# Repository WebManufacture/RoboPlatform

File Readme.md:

# RoboPlatform

#### Общее

Универсальная платформа для построения систем цифровой автоматизации и роботизации. Платформа разрабатывается, как самостоятельный проект, развитие идеи Arduino. В качестве основных контроллеров, используемых в платформе, выбрана линейка контроллеров от компании ST Microelectronics (STM8, STM32 ARM).
Основные принципы и идеи платформы:

0. Возможность создания по большей части самовоспроизводимой системы модулей. Имеется ввиду, что на базе существующей системы модулей и инструментов можно создавать как свою копию, так и новые, перспективные.
1. Сделать компоненты настолько дешевыми, чтобы их можно было использовать свободно, как "кирпичики" для построения сложных систем, состоящих из огромного числа отлаженных модулей. Также дешевизна и простота модулей, делает возможным их применение в условиях кризиса или бесконечно-малого финансирования.
2. По контроллеру - в каждый узел! Идея состоит в том, чтобы создать общее программное облако, с помощью которого, можно создавать самоконфигурируемые, самособирающиеся, самотестируемые и другие системы, требующие интерактивности от каждого своего функционального узла от мала до велика. Благо, современная конкуренция на рынке контроллеров дает возможность приобретать 8ми разрядные контроллеры по цене < $0.5, и ARM-контолллеры от 1$.
3. Облегчение и автоматизация труда разработчика. Предполагается применение разработок Web-Manufacture.net (KLAB, HLAB, ILAB и прочих), а также создание современных систем управления, разработки и тестирования для этой платформы. Под "современностью" понимается использования опыта разработки для систем более высокого уровня, применительно, к несколько "поотставшей" области программирования и отладки систем на контроллерах.
4. Использовать коммуникационные протоколы и принципы проекта ILAB
5. "Селективная шина" в качестве основной модели взаимодействия 

#### Текущая стадия и план.

На сегодня разработана и продумана общая концепция проекта. Проект разбит на несколько автономных, но взаимосвязанных подпроектов. Наибольший прогресс в области создания ПО, в частности распределенной клиент-серверной инфраструктуры и пользовательских интерфейсов. 
Реализованы “в железе” основные модули и базовый набор инстументов проекта, как то RoboMotors, RoboMind, RoboPwm, RoboPower, являющиеся концептуальными наследниками своих программных прототипов. 
Некоторые подпроекты уже имеют собственную жизнь, как RoboCNC, RoboPainter и RoboRails, трудящееся в автоматизированых теплицах.
В рамках платформы идет работа по 3м основным направлениям:

1. Инструменты и механическая часть, корпуса модулей, система соединения.
2. Адаптация модулей, для воспроизводства в системе на базе RoboCNC (#МФКС).
3. Доработка ПО, базирующееся на разработках Web-Manufacture (HLAB, ILAB, KLAB).

###### Шина XRouting

Шина представляет собой 4 вывода, 2 сигнальныx и 2 для питания. Каждый модуль может содержать несколько портов для подключения шины, но в целом это все равно остается одна физическая шина. Исключение -- контроллеры RoboMind. 

Одной из главных особенностей, как шины, так и протокола -- является "горячее" подключение модулей, а также их идентификация.

Протокол шины описан ниже

#### Модули

Система построена на модулях для у правления чем-то конкретным (освещением RoboLeds, двигателем RoboMotor, другими контроллерами RoboMind), которые подключаются к общей шине XRouting.
Также есть модули для считывания и запоминания информации (RoboSensor, RoboControl), а также ее обработки (RoboMind)

Для модулей используются разные контроллеры и процессоры, например
stm8s207rbt6, stm8l151c8t6, stm8af5288t, stm32f103cbt6, stm32f407vet6, stm32f756zg, stm32w108cbu64tr,
stm32h743vit6(перспективный).
Конроллеры других производителей: ESP8266, и другие
Или платформы Raspberry Pi, Orange Pi. 

###### RoboMind

Контроллер представляет собой некий "Мозг", который может управлять другими модулями RP, или заниматься переадресацией пакетов. Причем может делать это как автономно, так и в связке с компьютером или Web-интерфейсом.
Разные реализации могут иметь разные интерфейсы, как то:
USB, UART, COM, RS-485, I2C, SPI, CAN, HDMI, Bluetooth, ZigBee, Ethernet, Wi-Fi.
И естественно, выходы шины XRouting, причем возможно несколько "портов", каждый из которых образует свою независимую шину.

Также к некоторым модулям можно подключать дополнительно SD карту, или даже USB-OTG запоминающее устройство (да тот же HDD через переходник)

Идея модуля в том, что он может запоминать программу, которую необходимо выполнять, управляя периферией, как дирижер - оркестром. Например, в архитектурном макете данный контроллер руководит всей автоматизацией исполняя запрограммированную последовательность действий.

В ПО для контроллера используется интересный подход, как "набор прошивок", которые пользователь может свободно выбирать, и загружать через встроенный BootLoader. Таким образом из данного мозга можно сделать широкий спектр устройств. Например, существует прошивки, которая позволяют сделать из данного модуля логический анализатор, контроллер ЧПУ, контроллер общего назначения, работающий по временным интервалам. 

Главная особенность разработки с использованием таких модулей, заключается в ПО "Конфигуратор", которое позволяет в реальном времени собирать из таких кирпичиков конечное решение, и сконфигурировать каждый его узел. Или же, произвести отладку всего "оркестра". За счет общей шины, каждый узел может отчитываться "мозгу" или ПК о своем состоянии или конфигурации. Именно над этим конфигуратором сейчас идет работа..

И все это счастье стоит порядка 5$ за штуку в младших моделях! Или же 7$ на базе ARM!!! Но верхний потолок может доходить до 400$ за промышленные реализации.

###### RoboMotor
Универсальный контроллер для управления "любыми" двигателями, Stepper, DC, AC, BLDC

###### RoboCoils
Модификация предыдущего модуля с еще более расширенным функционалом управления любыми электромагнитными устройствами.

###### RoboCNC
Платформа для построения станков с ЧПУ, на базе предыдущих модулей

###### RoboPower
Управление системами хранения и конвертации электроэнергии. содержат разные DC-DC и системы контроля параметром V, I, P. Можно использовать для заряда, разряда аккумуляторов или объединения нескольких разных источников и потребителей энергии.

###### RoboPwm
Модуль для управления силовой нагрузкой с применением PID-алгоритмов
В модулях бывает до 8 портов для одновременного управления конечными устройствами (например, светодиодами, или нагревателями). С контролем параметров через V, I, P.

###### RoboLeds
Модификация предыдущего модуля для управления светодиодными линейками
Могут содержать до 64 портов.

###### RoboSensors
Аналоговые модули высокого разрешения использующиеся для систем мониторинга или измерения параметров техпроцесса.
Имеют до 4х аналоговых входов на модуль, иногда дифференциальных. 
Могут синхронизировать время измерения с другими модулями с высокой точностью. 
Также могут содержать обработчики DSP, топовые АЦП и ОУ от AD, чипы CPLD, FPGA от Altera серии MAX и Cyclone
Как правило построены на чипах STM8S903, STM32F3, F4, для расширения вычислительных мошностей используют ресурсы RoboMind 
 
###### RoboLogic
Модули логического взаимодействия и логического ввода. Аналог логических элементов. Построены на компараторах и могут быть использованы для ввода логической информации.
К примеру, логические анализаторы или системы мониторинга реального времени с высокоскоростной обработкой информации. 
Некоторые модули содержат чипы CPLD, FPGA от Altera серии MAX и Cyclone 
Бывают как дешевыми и простыми, так и дорогими и сложными.

###### RoboControl
Простые и дешевые варианты предыдущих модулей, к примеру для кнопочного ввода или простых датчиков.

###### RoboVision
Модули для работы с визуальной информацией, камерами, матрицами или устройствами вывода изображения. 

#### XRouting

Это -- протокол и сердце системы.

         (#xx | #1x)( #dstAddr ...,  #srcAddr..., #size, #pmo,#pm, #value,...,#pms, #pm, value..., #pme, #pme, (#crc) ? #03
         1x - XRT packet type

             11 Hi (Hi, when raise node)
             12 Dying (Something wrong, buy or error, Unscribe, Del)
             13 Acknowledge (Response, for anything, for example "see you as")
             14 Things (Get Description, Get anything, Add, Set)
             15 Lookup (All, Subscribe)
             16 Redirect (Info)
             17 Forward  (Note)
             18 Tunnel

         xx #SYNC
             #A0-#A9 - #Req
             #B0-#B9 - #Ack
             #C0-#C9 - Reserved
             #E0-#EF   #syncData1 #syncData2
             #F0-FF    #syncData (1Byte)

         #addr (#dstAddr, #srcAddr)
             First 1bits of address means this is end of address chain
             0 - packet chain
             1 - end packet
             Special bytes in packet chain may have sense -- delimeter, mark of the address type

         pm = packet marker ( 3bit - dataType + 5bit thing identifier )
              pm data types:

              00 - Raw Data, for a strings or something encoded, looking the next PM
              01 - Sized    something have fixed size, things identifier describe size
              10 - #pmo Complex start with another PM's
              11 - #pme Complex End

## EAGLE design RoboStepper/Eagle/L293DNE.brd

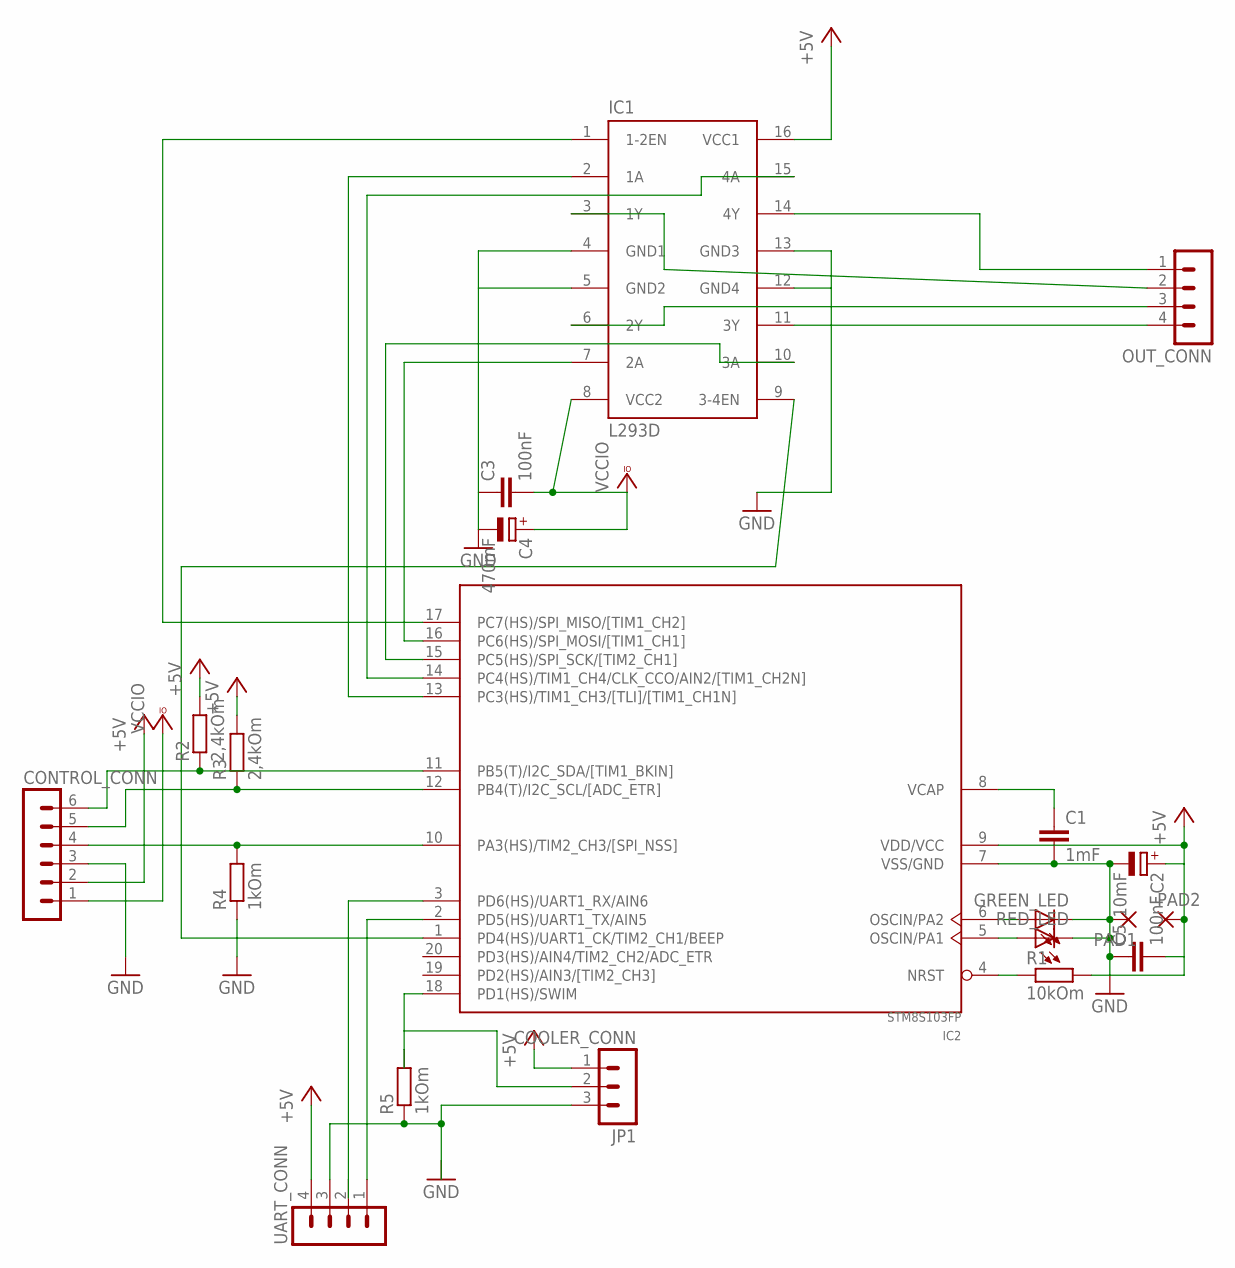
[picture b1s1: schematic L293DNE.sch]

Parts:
C1: 1mF; C0805
C2: 10mF; SMC_C
C3, C5: 100nF; C1206
C4: 470mF; E2,5-5
CONTROL_CONN: MA06-1
GREEN_LED: LEDSML0805; SML0805
IC1: L293D; DIL16
IC2: STM8S103FP; TSSOP20
JP1: COOLER_CONN; MA03-1
OUT_CONN: MA04-1
PAD1, PAD2: SMD2; SMD1,27-2,54
R1: 10kOm; R0805
R2, R3: 2,4kOm; R0805
R4, R5: 1kOm; R0805
RED_LED: LEDSML0805; SML0805
UART_CONN: MA04-1

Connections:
+5V: C2.+, C5.2, CONTROL_CONN.2, IC1.16 (VCC1), IC2.9 (VDD/VCC), JP1.1, PAD2.1, R1.2, R2.2, R3.2, UART_CONN.4
DIR\I2C_SCL: CONTROL_CONN.5, IC2.12 (PB4(T)/I2C_SCL/[ADC_ETR]), R3.1
EN: CONTROL_CONN.4, IC2.10 (PA3(HS)/TIM2_CH3/[SPI_NSS]), R4.2
GND: C1.2, C2.-, C3.1, C4.-, C5.1, CONTROL_CONN.3, GREEN_LED.C, IC1.4 (GND1), IC1.5 (GND2), IC1.12 (GND4), IC1.13 (GND3), IC2.7 (VSS/GND), JP1.3, PAD1.1, R4.1, R5.1, RED_LED.C, UART_CONN.3
unnamed: IC2.18 (PD1(HS)/SWIM), JP1.2, R5.2
unnamed: IC1.14 (4Y), OUT_CONN.1
unnamed: IC1.15 (4A), IC2.14 (PC4(HS)/TIM1_CH4/CLK_CCO/AIN2/[TIM1_CH2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)
unnamed: IC1.10 (3A), IC2.15 (PC5(HS)/SPI_SCK/[TIM2_CH1])
unnamed: IC1.7 (2A), IC2.16 (PC6(HS)/SPI_MOSI/[TIM1_CH1])
unnamed: IC1.2 (1A), IC2.13 (PC3(HS)/TIM1_CH3/[TLI]/[TIM1_CH1N])
unnamed: IC1.9 (3-4EN), IC2.1 (PD4(HS)/UART1_CK/TIM2_CH1/BEEP)
unnamed: IC1.3 (1Y), OUT_CONN.2
unnamed: C1.1, IC2.8 (VCAP)
unnamed: IC2.4 (NRST), R1.1
unnamed: IC2.5 (OSCIN/PA1), RED_LED.A
unnamed: GREEN_LED.A, IC2.6 (OSCIN/PA2)
unnamed: IC1.6 (2Y), OUT_CONN.3
unnamed: IC2.2 (PD5(HS)/UART1_TX/AIN5), UART_CONN.1
unnamed: IC2.3 (PD6(HS)/UART1_RX/AIN6), UART_CONN.2
unnamed: IC1.11 (3Y), OUT_CONN.4
STEP\I2C_SDA: CONTROL_CONN.6, IC2.11 (PB5(T)/I2C_SDA/[TIM1_BKIN]), R2.1
VCCIO: C3.2, C4.+, CONTROL_CONN.1, IC1.8 (VCC2)

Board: 2 copper layers, 20 parts (0 on the bottom side), 22 nets, no tracks yet.

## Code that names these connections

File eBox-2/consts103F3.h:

#ifndef _Hardware_Ext
#define _Hardware_Ext

#include "STM8S103F3P.h"
#include "Consts.h"

#define taskHigh 255
#define portCount 16

#define UART_CR1 UART1_CR1
#define UART_CR2 UART1_CR2
#define UART_CR3 UART1_CR3
#define UART_CR4 UART1_CR4
#define UART_CR5 UART1_CR5
#define UART_BRR2 UART1_BRR2
#define UART_BRR1 UART1_BRR1
#define UART_SR UART1_SR
#define UART_DR UART1_DR

#define SysR1 PD.Out |= bit2
#define SysR0 PD.Out &= ~bit2
#define SysG1 PD.Out |= bit3
#define SysG0 PD.Out &= ~bit3
#define SysB1 PD.Out |= bit1
#define SysB0 PD.Out &= ~bit1
       
@near unsigned char bits[27] = {
 bit1,//0     PD1
 bit1,//1     PA1
 bit2,//2     PA2
 bit3,//3     PA3
 bit4,//4     PB4
 bit5,//5     PB5
 bit3,//6     PC3
 bit4,//7     PC4
 bit5,//8     PC5
 bit6,//9     PC6
 bit7,//10    PC7
 bit2,//11    PD2
 bit3,//12    PD3
 bit4,//13    PD4
 bit5,//14    PD5
 bit6 //15    PD6
};            

@near struct Pins *pins[27] = {
	&PpD,//0    PD1
	&PpA,//1    PA1
	&PpA,//2    PA2
  &PpA,//3    PA3
	&PpB,//4    PB4
	&PpB,//5    PB5
	&PpC,//6    PC3
	&PpC,//7    PC4
	&PpC,//8    PC5
	&PpC,//9    PC6
	&PpC,//10   PC7
	&PpD,//11   PD2
	&PpD,//12   PD3
	&PpD,//13   PD4
	&PpD,//14   PD5
	&PpD //15   PD6
};        

@near struct Port * ports[27] = {
	&PD,//0    PD1
	&PA,//1    PA1
	&PA,//2    PA2
  &PA,//3    PA3
	&PB,//4    PB4
	&PB,//5    PB5
	&PC,//6    PC3
	&PC,//7    PC4
	&PC,//8    PC5
	&PC,//9    PC6
	&PC,//10   PC7
	&PD,//11   PD2
	&PD,//12   PD3
	&PD,//13   PD4
	&PD,//14   PD5
	&PD //15   PD6
};                 

#endif

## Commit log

2014-04-17 Last Version with callbacks
2014-11-03 Working copy with time parameter.
2014-11-04 Worked ver vith async motor. Prepare to ASM
2016-02-23 Added files via upload
2019-09-30 Actualization
2019-09-30 Movies and RoboPlatform object protocol integrated
2019-09-30 RoboPlatform object protocol Description
2019-10-01 XRouting protocol description
2019-10-01 RoboEmulator & CellsManager
2019-10-01 RoboPlatform description
